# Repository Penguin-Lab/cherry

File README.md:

# cherry
Um robô hexapod controlado por uma ESP32 automático ou remotamente. Nossa cereja.
A Cherry é uma hexapod desenvolvida como uma evolução da Tiffany e da Scarlet. O intuito é adicionar uma IMU e mover a bateria para o interior do robô. A Cherry pode andar de forma autônoma, ser controlada pelo celular ou pelo nosso espaço inteligente por MQTT. Para se locomover, ela possui 6 patas de 3 graus de liberdade cada (3 motores) e uma ESP32 que comanda o conjunto! Ela é a nossa cereja, a irmã da Tiffany e da Scarlet e a nova integrante robótica do nosso espaço inteligente!

# Estrutura física
A estrutura física do robô é composta por seis patas de três eixos cada (três motores). As patas são fixadas a duas placas de PLA para deixar o robô firme. As peças são todas projetadas em 3D e foram impressas utilizando PLA, podendo ser encontradas na pasta "parts" deste projeto.

<table>
  <tr>
    <td></td>
    <td rowspan="2"></td>
  </tr>
  <tr>
    <td></td>
  </tr>
</table>

## Peças 3D em STL
As peças em 3D desenvolvidas para este projeto foram baseadas nos projetos das hexapods Tiffany e Scarlet. Na pasta "parts", estão listadas essas peças em STL. Para ajudar, segue abaixo uma lista de todas as peças que devem ser impressas e qual o valor da sua maior dimensão (para ajudar na escolha da impressora):

* Corpo
  * 1x [CHERRY_BODY_DOWN.STL (230 mm)](https://github.com/Penguin-Lab/cherry/blob/main/parts/CHERRY_BODY_DOWN.STL)
  * 1x [CHERRY_BODY_UP.STL (230 mm)](https://github.com/Penguin-Lab/cherry/blob/main/parts/CHERRY_BODY_UP.STL)
  * 1x [CHERRY_BODY_UP_BLOSSOMS.STL (113 mm)](https://github.com/Penguin-Lab/cherry/blob/main/parts/CHERRY_BODY_UP_BLOSSOMS.STL)
  * 1x [CHERRY_BODY_UP_BRANCH.STL (96 mm)](https://github.com/Penguin-Lab/cherry/blob/main/parts/CHERRY_BODY_UP_BRANCH.STL)
  * 1x [CHERRY_BODY_UP_LEAVES.STL (168 mm)](https://github.com/Penguin-Lab/cherry/blob/main/parts/CHERRY_BODY_UP_LEAVES.STL)
  * 1x [CHERRY_LOGO.STL (36 mm)](https://github.com/Penguin-Lab/cherry/blob/main/parts/CHERRY_LOGO.STL)
  * 2x [CHERRY_SPACER_FRONT.STL (33 mm)](https://github.com/Penguin-Lab/cherry/blob/main/parts/CHERRY_SPACER_FRONT.STL)
  * 2x [CHERRY_SPACER_CENTER.STL (64 mm)](https://github.com/Penguin-Lab/cherry/blob/main/parts/CHERRY_SPACER_CENTER.STL)
  * 1x [CHERRY_BATTERY_CASE.STL (164 mm)](https://github.com/Penguin-Lab/cherry/blob/main/parts/CHERRY_BATTERY_CASE.STL)
  * 1x [CHERRY_BATTERY_DOOR.STL (77 mm)](https://github.com/Penguin-Lab/cherry/blob/main/parts/CHERRY_BATTERY_DOOR.STL)
  * 1x [CHERRY_SUPORT_PLUGS_SWITCHES.STL (50 mm)](https://github.com/Penguin-Lab/cherry/blob/main/parts/CHERRY_SUPORT_PLUGS_SWITCHES.STL)
  * 1x [CHERRY_SUPORT_PLUGS_BATTERY.STL (67 mm)](https://github.com/Penguin-Lab/cherry/blob/main/parts/CHERRY_SUPORT_PLUGS_BATTERY.STL)
* Patas
  * 6x [CHERRY_TIBIA_LEFT.STL (171 mm)](https://github.com/Penguin-Lab/cherry/blob/main/parts/CHERRY_TIBIA_LEFT.STL)
  * 6x [CHERRY_TIBIA_RIGHT.STL (171 mm)](https://github.com/Penguin-Lab/cherry/blob/main/parts/CHERRY_TIBIA_RIGHT.STL)
  * 6x [CHERRY_TIBIA_MIDDLE.STL (61 mm)](https://github.com/Penguin-Lab/cherry/blob/main/parts/CHERRY_TIBIA_MIDDLE.STL)
  * 3x [CHERRY_SHIELD_A_LEFT.STL (145 mm)](https://github.com/Penguin-Lab/cherry/blob/main/parts/CHERRY_SHIELD_A_LEFT.STL)
  * 3x [CHERRY_SHIELD_A_RIGHT.STL (145 mm)](https://github.com/Penguin-Lab/cherry/blob/main/parts/CHERRY_SHIELD_A_RIGHT.STL)
  * 3x [CHERRY_SHIELD_B_LEFT.STL (145 mm)](https://github.com/Penguin-Lab/cherry/blob/main/parts/CHERRY_SHIELD_B_LEFT.STL)
  * 3x [CHERRY_SHIELD_B_RIGHT.STL (145 mm)](https://github.com/Penguin-Lab/cherry/blob/main/parts/CHERRY_SHIELD_B_RIGHT.STL)
  * 6x [CHERRY_FOOT.STL (25 mm)](https://github.com/Penguin-Lab/cherry/blob/main/parts/CHERRY_FOOT.STL)
  * 3x [CHERRY_FEMUR_FRONT_LEFT.STL (132 mm)](https://github.com/Penguin-Lab/cherry/blob/main/parts/CHERRY_FEMUR_FRONT_LEFT.STL)
  * 3x [CHERRY_FEMUR_FRONT_RIGHT.STL (132 mm)](https://github.com/Penguin-Lab/cherry/blob/main/parts/CHERRY_FEMUR_FRONT_RIGHT.STL)
  * 3x [CHERRY_FEMUR_BACK_LEFT.STL (132 mm)](https://github.com/Penguin-Lab/cherry/blob/main/parts/CHERRY_FEMUR_BACK_LEFT.STL)
  * 3x [CHERRY_FEMUR_BACK_RIGHT.STL (132 mm)](https://github.com/Penguin-Lab/cherry/blob/main/parts/CHERRY_FEMUR_BACK_RIGHT.STL)
  * 6x [CHERRY_FEMUR_MIDDLE.STL (51 mm)](https://github.com/Penguin-Lab/cherry/blob/main/parts/CHERRY_FEMUR_MIDDLE.STL)
  * 6x [CHERRY_OMBRO_DOWN.STL (97 mm)](https://github.com/Penguin-Lab/cherry/blob/main/parts/CHERRY_OMBRO_DOWN.STL)
  * 3x [CHERRY_OMBRO_UP_LEFT.STL (97 mm)](https://github.com/Penguin-Lab/cherry/blob/main/parts/CHERRY_OMBRO_UP_LEFT.STL)
  * 3x [CHERRY_OMBRO_UP_RIGHT.STL (97 mm)](https://github.com/Penguin-Lab/cherry/blob/main/parts/CHERRY_OMBRO_UP_RIGHT.STL)
* Motor
  * 12x [CHERRY_TAMPA_MOTOR_DS3230.STL (40 mm)](https://github.com/Penguin-Lab/cherry/blob/main/parts/CHERRY_TAMPA_MOTOR_DS3230.STL)

Obs: a tampa de 12 motores deverão ser trocadas pelas peças [CHERRY_TAMPA_MOTOR_DS3230.STL (41 mm)](https://github.com/Penguin-Lab/cherry/blob/main/parts/CHERRY_TAMPA_MOTOR_DS3230.STL) para que seja possível fixar os rolamentos nas patas. Serão utilizados 3 rolamentos por pata:

Obs 2: os motores ficam fixados nas peças por [discos metálicos pequenos padrão para eixos de servo](https://a.aliexpress.com/_mPHt3nf).

## Outros itens da estrutura
Alguns outros itens são necessários para finalizar a estrutura da Cherry:
* 6x Parafusos m4 de 90 mm com porca autotravante: fechar o robô prendendo as peças [CHERRY_BODY_UP.STL](https://github.com/Penguin-Lab/cherry/blob/main/parts/CHERRY_BODY_UP.STL), [CHERRY_BODY_DOWN.STL](https://github.com/Penguin-Lab/cherry/blob/main/parts/CHERRY_BODY_DOWN.STL), [CHERRY_SPACER_FRONT.STL](https://github.com/Penguin-Lab/cherry/blob/main/parts/CHERRY_SPACER_FRONT.STL), [CHERRY_SPACER_CENTER.STL](https://github.com/Penguin-Lab/cherry/blob/main/parts/CHERRY_SPACER_CENTER.STL), [CHERRY_BATTERY_CASE.STL](https://github.com/Penguin-Lab/cherry/blob/main/parts/CHERRY_BATTERY_CASE.STL), [CHERRY_BATTERY_DOOR.STL](https://github.com/Penguin-Lab/cherry/blob/main/parts/CHERRY_BATTERY_DOOR.STL), [CHERRY_SUPORT_PLUGS_SWITCHES.STL](https://github.com/Penguin-Lab/cherry/blob/main/parts/CHERRY_SUPORT_PLUGS_SWITCHES.STL) e [CHERRY_SUPORT_PLUGS_BATTERY.STL](https://github.com/Penguin-Lab/cherry/blob/main/parts/CHERRY_SUPORT_PLUGS_BATTERY.STL)
* 24x Parafusos m4 de 55 mm com porca: fechar os ombros prendendo as peças [CHERRY_OMBRO_DOWN.STL](https://github.com/Penguin-Lab/cherry/blob/main/parts/CHERRY_OMBRO_DOWN.STL) com as peças [CHERRY_OMBRO_UP_LEFT.STL](https://github.com/Penguin-Lab/cherry/blob/main/parts/CHERRY_OMBRO_UP_LEFT.STL) e [CHERRY_OMBRO_UP_RIGHT.STL](https://github.com/Penguin-Lab/cherry/blob/main/parts/CHERRY_OMBRO_UP_RIGHT.STL)
* 12x Parafusos m4 de 50 mm com porca: fechar os ombros prendendo as peças [CHERRY_OMBRO_DOWN.STL](https://github.com/Penguin-Lab/cherry/blob/main/parts/CHERRY_OMBRO_DOWN.STL) com as peças [CHERRY_OMBRO_UP_LEFT.STL](https://github.com/Penguin-Lab/cherry/blob/main/parts/CHERRY_OMBRO_UP_LEFT.STL) e [CHERRY_OMBRO_UP_RIGHT.STL](https://github.com/Penguin-Lab/cherry/blob/main/parts/CHERRY_OMBRO_UP_RIGHT.STL)
* Diversos parafusos m3
* 6x Tiras de EVA: colocar na ponta das peças [CHERRY_FOOT.STL](https://github.com/Penguin-Lab/cherry/blob/main/parts/CHERRY_FOOT.STL) para evitar que o robô deslize
* Arruelas entre as porcas e a peça [CHERRY_BODY_DOWN.STL](https://github.com/Penguin-Lab/cherry/blob/main/parts/CHERRY_BODY_DOWN.STL)

## Placa de circuito impresso
No projeto, foi desenvolvida uma placa de circuito para servir como shield para a ESP32 e conexão com um hub i2c (que conecta as duas placas PCA9685 e a IMU ao microcontrolador), com o DFPlayer Mini MP3 Player, com o calibrador de motores e com a fita de cobre (como sensor de toque do robô).

## Calibração dos motores
A calibração dos motores é feita utilizando o [CALIBRADOR DE MOTORES](https://github.com/Penguin-Lab/calib_servomotor) conectado às PCAs da Cherry. Isso deve ser feito pelo clock das PCAs ser diferente de uma placa para outra. Logo, os motores da esquerda são calibrados utilizando a PCA da esquerda e os da direita com a PCA da direita. Os valores retornados pela calibração são jogados nesta [PLANILHA](https://docs.google.com/spreadsheets/d/1Kh9AVbb79lXnJq5dlCiB7NEVVmcJWRX6X2CdDR9_QZo/edit?gid=885718543). A planilha ajeita os valores de PWM retornados na IDE do Arduino para valores que representem 0 e 180 graus dos motores já na estrutura das patas. Esses valores são os mesmos listados no código de comando da Cherry.

## Componentes eletrônicos
Os componentes eletrônicos embarcados no robô e equipamentos utilizados estão listados abaixo.
* Controlador com Wi-fi e Bluetooth
  * 1x ESP32 (38 pinos)
* Motores
  * 18x Servo DS3230 PRO-180
* 2x Placas PCA9685 para comando dos 18 motores (9 motores em cada)
* Chave (switch)
* Chave pequena (switch)
* Alimentação
  * Regulador para 5V (ESP32)
  * Regulador HV SBEC YPG 20A configurado para saída de 6V (motores)
  * Bateria LiPo 5000mAh 3s 11,1V (motores)
* Módulo de hub i2c
* Fita de folha de cobre de 3mm
* Módulo GY-BNO080
* Imãs para a tampa do case de bateria
* Autofalante de 4 Ohm e 3 W

# Software
A programação da ESP32 utiliza a biblioteca chamada PenguinLib disponível na Arduino IDE, também desenvolvida pelo laboratório. Tanto os códigos de calibração de motores, quanto os de utilização do hardware e comando do robô estão disponíveis como exemplos nesta biblioteca.

Na pasta "codes", há dois exemplos de programação da ESP32 (38 pinos). Eles são exemplos em C++ do comando de movimentação da Cherry:
* Dabble: a ESP32 pode se comunicar com o aplicativo Dabble no celular e receber comandos de ação;
* Espaço Inteligente (IS): a ESP32 pode se comunicar com o Espaço Inteligente por MQTT e receber esses mesmos comandos.

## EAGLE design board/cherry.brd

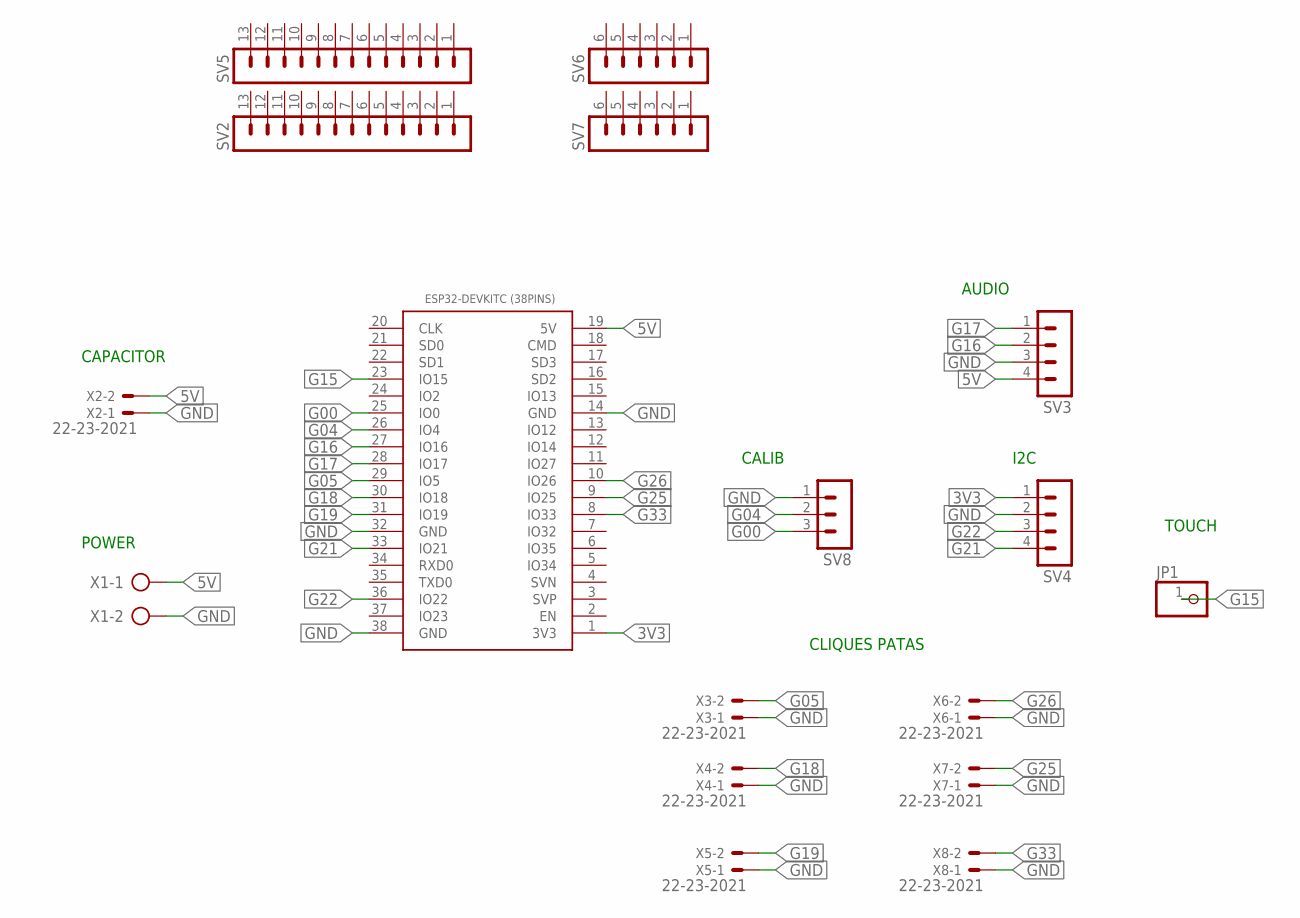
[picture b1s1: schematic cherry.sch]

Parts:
ESP32-DEVKITC(38PINS)1: ESP32DEVKITC_38PINS; ESP32-DEVKITC
JP1: PINHD-1X1; 1X01
SV2, SV5: MA13-1
SV3, SV4: MA04-1
SV6, SV7: MA06-1
SV8: MA03-1
X1: AK300/2
X2, X3, X4, X5, X6, X7, X8: 22-23-2021

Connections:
3V3: ESP32-DEVKITC(38PINS)1.1 (3V3), SV4.1
5V: ESP32-DEVKITC(38PINS)1.19 (5V), SV3.4, X1.1, X2.2
G00: ESP32-DEVKITC(38PINS)1.25 (IO0), SV8.3
G04: ESP32-DEVKITC(38PINS)1.26 (IO4), SV8.2
G05: ESP32-DEVKITC(38PINS)1.29 (IO5), X3.2
G15: ESP32-DEVKITC(38PINS)1.23 (IO15), JP1.1
G16: ESP32-DEVKITC(38PINS)1.27 (IO16), SV3.2
G17: ESP32-DEVKITC(38PINS)1.28 (IO17), SV3.1
G18: ESP32-DEVKITC(38PINS)1.30 (IO18), X4.2
G19: ESP32-DEVKITC(38PINS)1.31 (IO19), X5.2
G21: ESP32-DEVKITC(38PINS)1.33 (IO21), SV4.4
G22: ESP32-DEVKITC(38PINS)1.36 (IO22), SV4.3
G25: ESP32-DEVKITC(38PINS)1.9 (IO25), X7.2
G26: ESP32-DEVKITC(38PINS)1.10 (IO26), X6.2
G33: ESP32-DEVKITC(38PINS)1.8 (IO33), X8.2
GND: ESP32-DEVKITC(38PINS)1.14 (GND), ESP32-DEVKITC(38PINS)1.32 (GND), ESP32-DEVKITC(38PINS)1.38 (GND), SV3.3, SV4.2, SV8.1, X1.2, X2.1, X3.1, X4.1, X5.1, X6.1, X7.1, X8.1

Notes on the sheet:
CAPACITOR
POWER
I2C
AUDIO
CALIB
CLIQUES PATAS
TOUCH

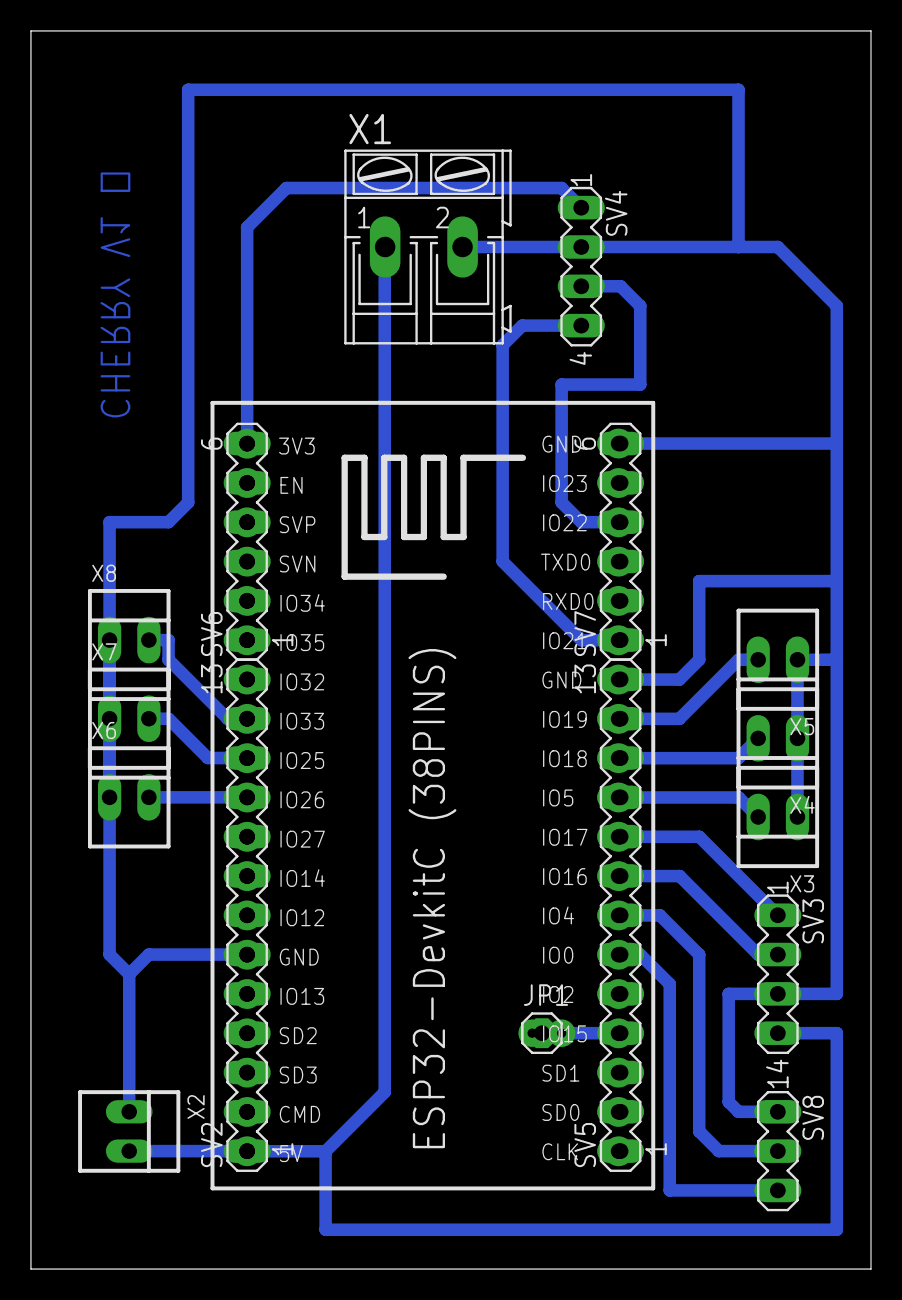
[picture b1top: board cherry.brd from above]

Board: 2 copper layers, 54.3 x 80.0 mm, 17 parts (0 on the bottom side), 16 nets.
